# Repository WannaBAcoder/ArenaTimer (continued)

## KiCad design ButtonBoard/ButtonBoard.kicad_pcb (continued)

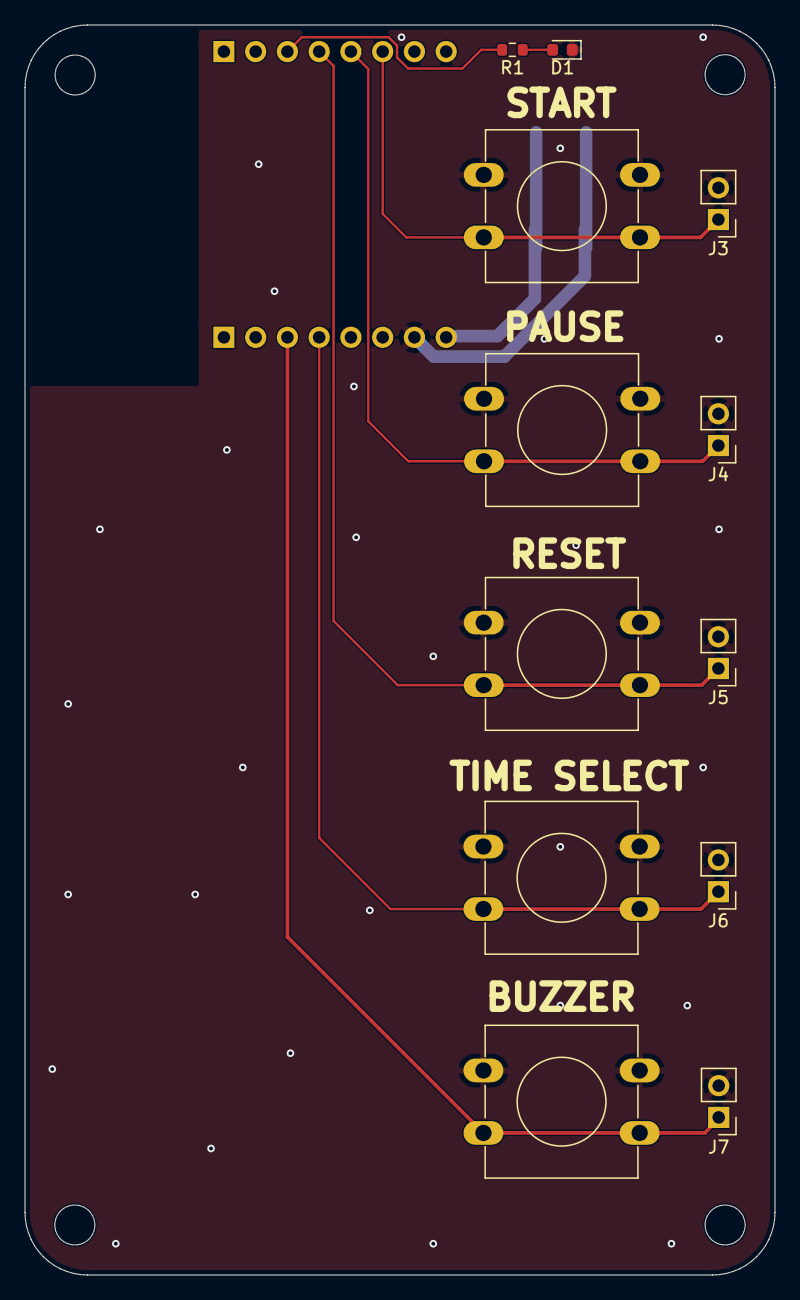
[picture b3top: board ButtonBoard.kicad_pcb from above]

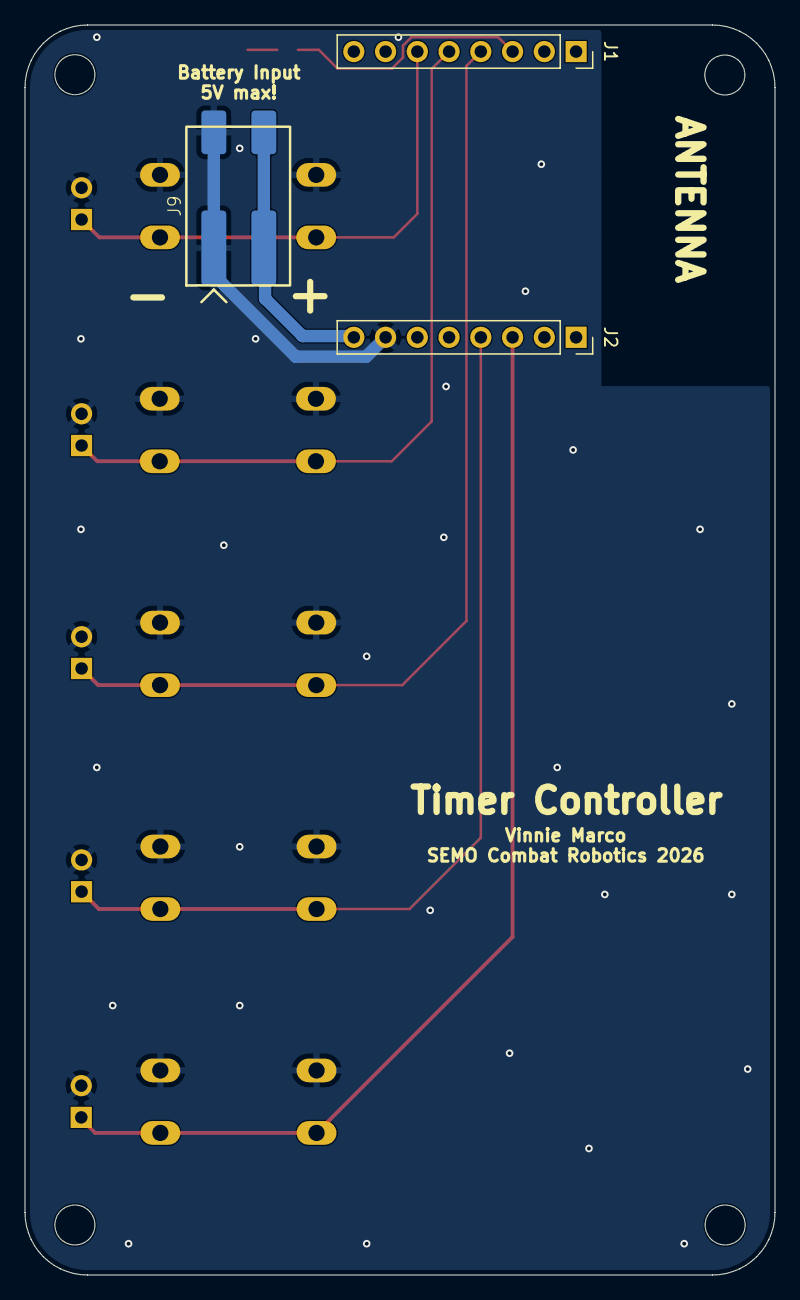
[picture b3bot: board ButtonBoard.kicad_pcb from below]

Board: 2 copper layers, 60.0 x 100.0 mm, 19 parts (3 on the bottom side), 9 nets.

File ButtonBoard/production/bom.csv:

Designator,Footprint,Quantity,Value,LCSC Part #
D1,0603,1,Red,C2286
"J1, J2",PinSocket_1x08_P2.54mm_Vertical,2,Conn_01x08_Socket,C42431840
J9,2060-452_998-404,1,WAGO,C2765055
R1,0603,1,470,C23179
SW1,SW_PUSH-12mm,1,START,C2888699 
SW2,SW_PUSH-12mm,1,PAUSE,C2888699 
SW3,SW_PUSH-12mm,1,RESET,C2888699 
SW4,SW_PUSH-12mm,1,TIME_SEL,C2888699 
SW5,SW_PUSH-12mm,1,BUZZER,C2888699

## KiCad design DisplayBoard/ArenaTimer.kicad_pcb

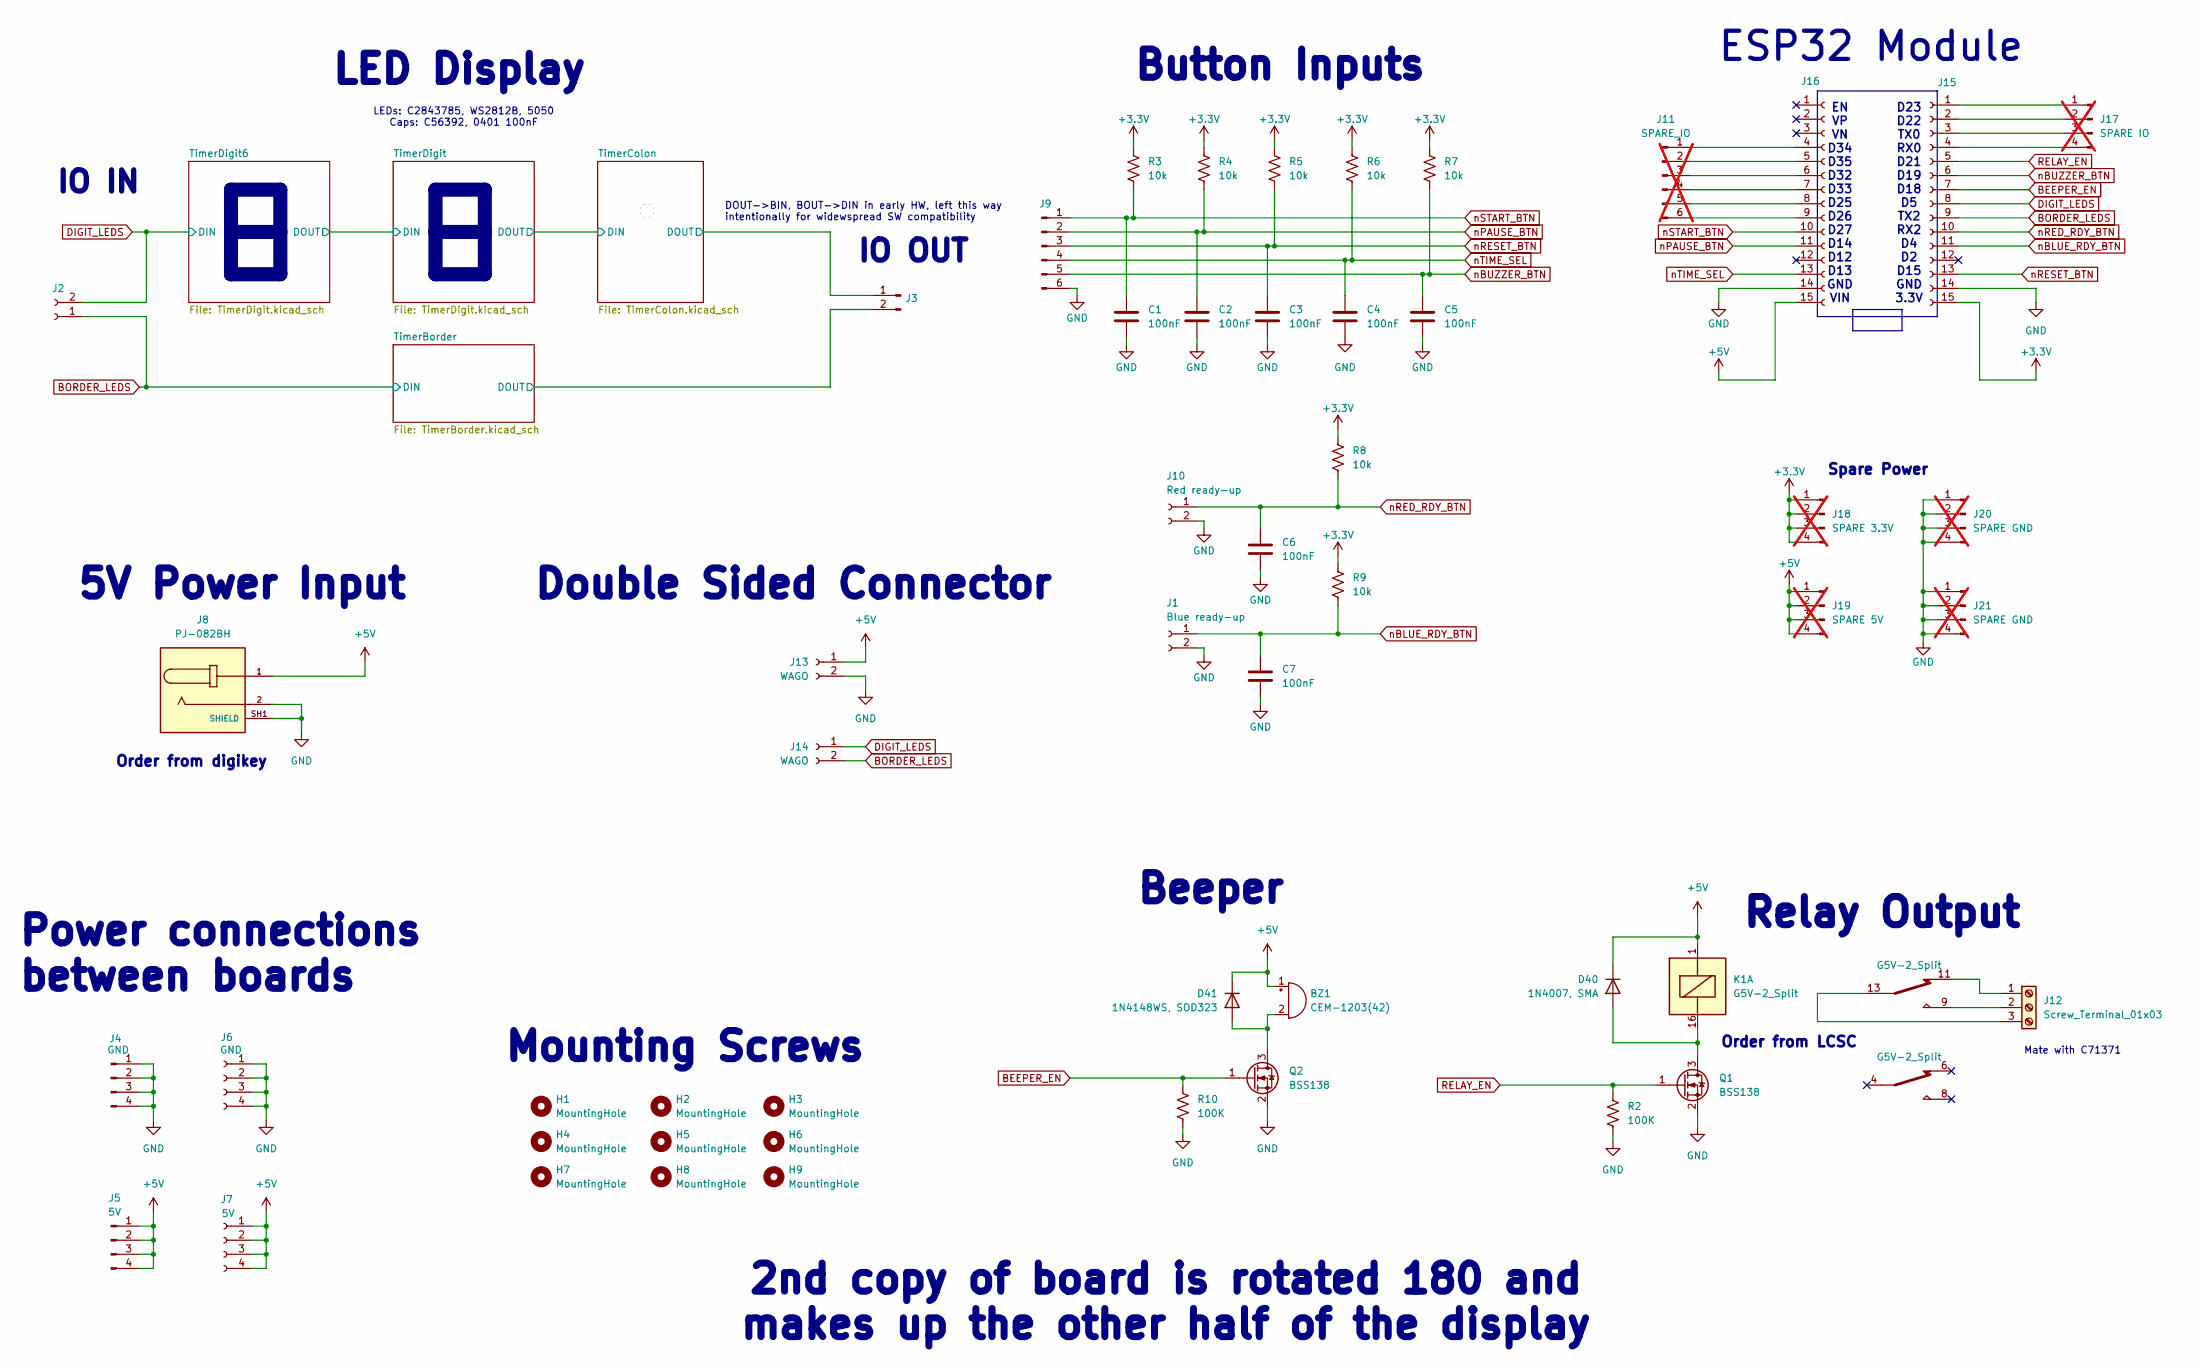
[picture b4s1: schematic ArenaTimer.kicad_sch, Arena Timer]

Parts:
BZ1: CEM-1203(42); Buzzer_TDK_PS1240P02BT_D12.2mm_H6.5mm; LCSC C3812098
C1, C2, C3, C4, C5, C6, C7: 100nF; C_0402_1005Metric; LCSC C1581
D40: 1N4007, SMA; D_SMA; LCSC C727081
D41: 1N4148WS, SOD323; D_SOD-323; LCSC C2128
H1, H2, H3, H4, H5, H6, H7, H8, H9: MountingHole; MountingHole_3.2mm_M3
J1: Blue ready-up; JST_EH_S2B-EH_1x02_P2.50mm_Horizontal; LCSC C19271377
J2: Conn_01x02_Socket; PinSocket_1x02_P2.54mm_Horizontal; LCSC C2897384
J3: Conn_01x02_Pin; PinHeader_1x02_P2.54mm_Horizontal; LCSC C492410
J4: GND; PinHeader_1x04_P2.54mm_Horizontal; LCSC C492412
J5: 5V; PinHeader_1x04_P2.54mm_Horizontal; LCSC C492412
J6: GND; PinSocket_1x04_P2.54mm_Horizontal; LCSC C2897386
J7: 5V; PinSocket_1x04_P2.54mm_Horizontal; LCSC C2897386
J8: PJ-082BH; SAMESKY_PJ-082BH; PARTREV 1.06; LCSC C3094233
J9: Conn_01x06_Pin; JST_EH_S6B-EH_1x06_P2.50mm_Horizontal; LCSC C157919
J10: Red ready-up; JST_EH_S2B-EH_1x02_P2.50mm_Horizontal; LCSC C19271377
J11: SPARE_IO; PinHeader_1x06_P2.54mm_Vertical; not fitted
J12: Screw_Terminal_01x03; TerminalBlock_MaiXu_MX126-5.0-03P_1x03_P5.00mm; LCSC C8377
J13, J14: WAGO; 2060-452_998-404; LCSC C2765055
J15, J16: Conn_01x15_Socket; PinSocket_1x15_P2.54mm_Vertical; LCSC C124408
J17: SPARE IO; PinHeader_1x04_P2.54mm_Vertical; not fitted
J18: SPARE 3.3V; PinHeader_1x04_P2.54mm_Vertical; not fitted
J19: SPARE 5V; PinHeader_1x04_P2.54mm_Vertical; not fitted
J20, J21: SPARE GND; PinHeader_1x04_P2.54mm_Vertical; not fitted
K1: G5V-2_Split; Relay_DPDT_Omron_G5V-2; LCSC C27269
Q1, Q2: BSS138; SOT-323_SC-70; LCSC C5224279
R2, R10: 100K; R_0402_1005Metric; LCSC C25530
R3, R4, R5, R6, R7, R8, R9: 10k; R_0402_1005Metric; LCSC C25744

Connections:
+3.3V: J15.15, J18.1, J18.2, J18.3, J18.4, R3.1, R4.1, R5.1, R6.1, R7.1, R8.1, R9.1
+5V: BZ1.1 (+), D40.1 (K), D41.1 (K), J5.1, J5.2, J5.3, J5.4, J7.1, J7.2, J7.3, J7.4, J8.1, J13.1, J16.15, J19.1, J19.2, J19.3, J19.4, K1.1; also elsewhere on the board
/TimerBorder/DOUT: J3.2; also elsewhere on the board
/TimerColon/DOUT: J3.1; also elsewhere on the board
BEEPER_EN: J15.7, Q2.1 (G), R10.1
BORDER_LEDS: J2.1, J14.2, J15.9; also elsewhere on the board
DIGIT_LEDS: J2.2, J14.1, J15.8; also elsewhere on the board
GND: C1.2, C2.2, C3.2, C4.2, C5.2, C6.2, C7.2, J1.2, J4.1, J4.2, J4.3, J4.4, J6.1, J6.2, J6.3, J6.4, J8.2, J8.SH1 (SHIELD), J8.SH2 (SHIELD), J8.SH3 (SHIELD), J8.SH4 (SHIELD), J9.6, J10.2, J13.2, J15.14, J16.14, J20.1, J20.2, J20.3, J20.4, J21.1, J21.2, J21.3, J21.4, Q1.2 (S), Q2.2 (S), R2.2, R10.2; also elsewhere on the board
unnamed: BZ1.2 (-), D41.2 (A), Q2.3 (D)
unnamed: D40.2 (A), K1.16, Q1.3 (D)
unnamed: J11.1, J16.4
unnamed: J11.2, J16.5
unnamed: J11.3, J16.6
unnamed: J11.4, J16.7
unnamed: J11.5, J16.8
unnamed: J11.6, J16.9
unnamed: J12.1, K1.11
unnamed: J12.2, K1.9
unnamed: J12.3, K1.13
unnamed: J15.1, J17.1
unnamed: J15.2, J17.2
unnamed: J15.3, J17.3
unnamed: J15.4, J17.4
RELAY_EN: J15.5, Q1.1 (G), R2.1
nBLUE_RDY_BTN: C7.1, J1.1, J15.11, R9.2
nBUZZER_BTN: C5.1, J9.5, J15.6, R7.2
nPAUSE_BTN: C2.1, J9.2, J16.11, R4.2
nRED_RDY_BTN: C6.1, J10.1, J15.10, R8.2
nRESET_BTN: C3.1, J9.3, J15.13, R5.2
nSTART_BTN: C1.1, J9.1, J16.10, R3.2
nTIME_SEL: C4.1, J9.4, J16.13, R6.2

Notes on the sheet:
Spare Power
EN VP VN D34 D35 D32 D33 D25 D26 D27 D14 D12 D13 GND VIN
Order from digikey
Mate with C71371
IO IN
Beeper
Power connections between boards
5V Power Input
Order from LCSC
IO OUT
Double Sided Connector
2nd copy of board is rotated 180 and makes up the other half of the display
Relay Output
Button Inputs
Mounting Screws
D23 D22 TX0 RX0 D21 D19 D18 D5 TX2 RX2 D4 D2 D15 GND 3.3V
LEDs: C2843785, WS2812B, 5050 Caps: C56392, 0401 100nF
ESP32 Module
DOUT->BIN, BOUT->DIN in early HW, left this way intentionally for widewspread SW compatibility
LED Display

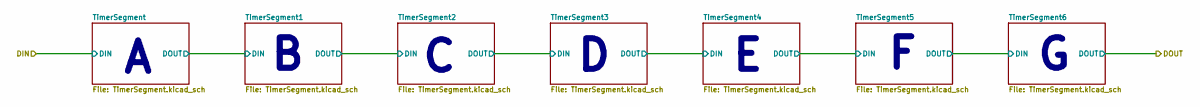
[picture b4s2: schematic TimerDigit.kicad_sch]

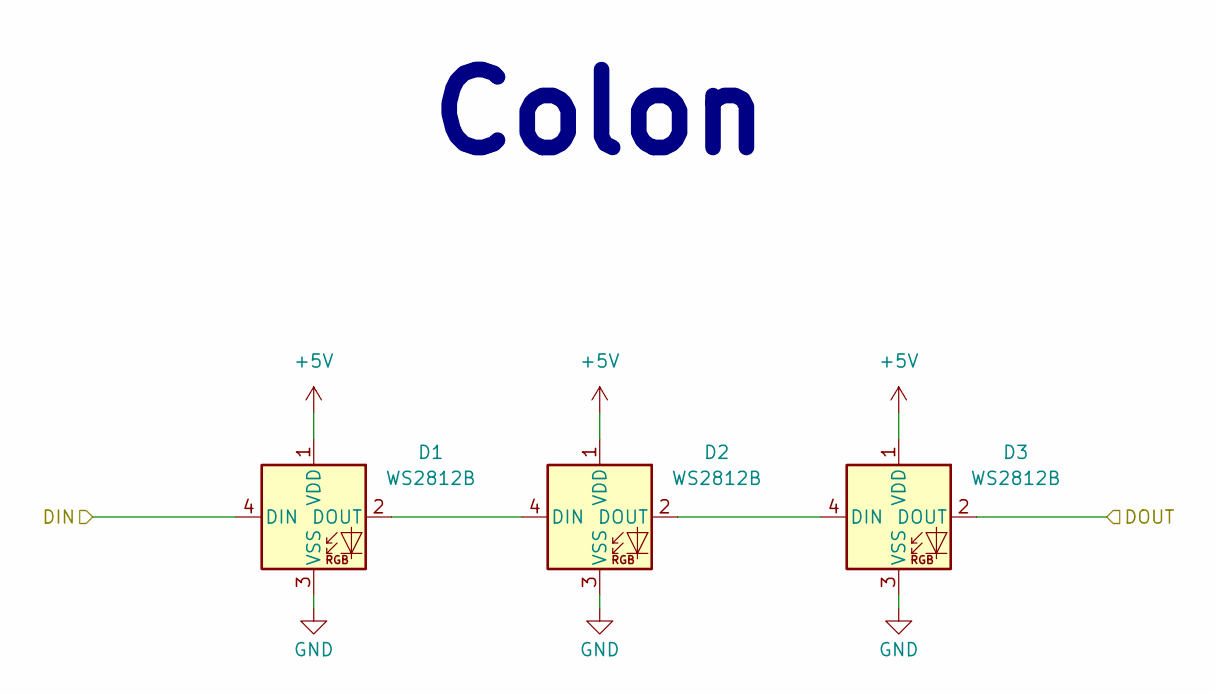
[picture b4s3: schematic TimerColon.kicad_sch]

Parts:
D1, D2, D3: WS2812B; LED_WS2812B_PLCC4_5.0x5.0mm_P3.2mm; LCSC C2843785

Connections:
+5V: D1.1 (VDD), D2.1 (VDD), D3.1 (VDD); also elsewhere on the board
/TimerColon/DIN: D1.4 (DIN); also elsewhere on the board
/TimerColon/DOUT: D3.2 (DOUT); also elsewhere on the board
GND: D1.3 (VSS), D2.3 (VSS), D3.3 (VSS); also elsewhere on the board
unnamed: D1.2 (DOUT), D2.4 (DIN)
unnamed: D2.2 (DOUT), D3.4 (DIN)

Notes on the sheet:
Colon

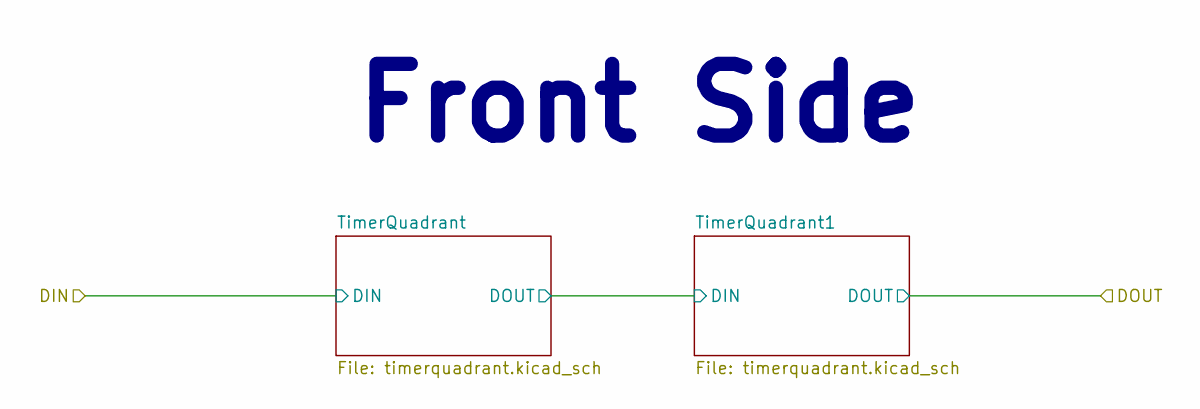
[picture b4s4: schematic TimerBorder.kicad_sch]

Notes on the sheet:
Front Side

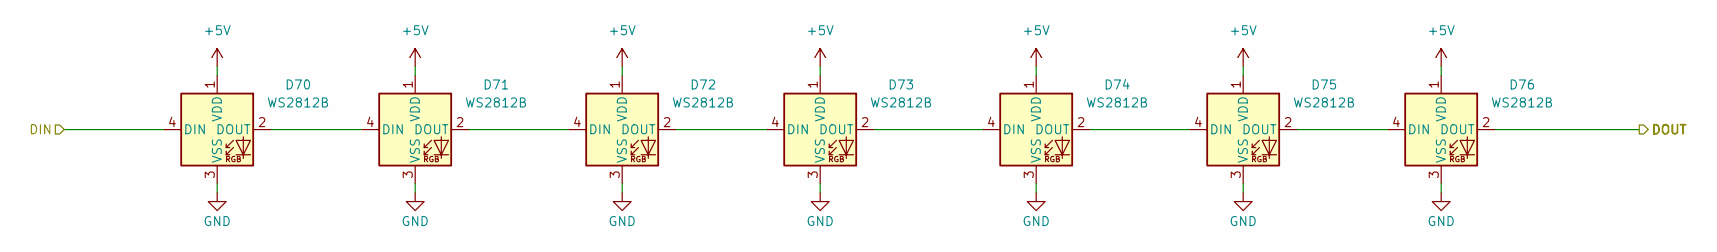
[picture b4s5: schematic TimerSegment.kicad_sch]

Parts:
D70, D71, D72, D73, D74, D75, D76: WS2812B; LED_WS2812B_PLCC4_5.0x5.0mm_P3.2mm; LCSC C2843785

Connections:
+5V: D70.1 (VDD), D71.1 (VDD), D72.1 (VDD), D73.1 (VDD), D74.1 (VDD), D75.1 (VDD), D76.1 (VDD); also elsewhere on the board
/TimerDigit/DIN: D70.4 (DIN); also elsewhere on the board
/TimerDigit/TimerSegment/DOUT: D76.2 (DOUT); also elsewhere on the board
GND: D70.3 (VSS), D71.3 (VSS), D72.3 (VSS), D73.3 (VSS), D74.3 (VSS), D75.3 (VSS), D76.3 (VSS); also elsewhere on the board
unnamed: D70.2 (DOUT), D71.4 (DIN)
unnamed: D71.2 (DOUT), D72.4 (DIN)
unnamed: D72.2 (DOUT), D73.4 (DIN)
unnamed: D73.2 (DOUT), D74.4 (DIN)
unnamed: D74.2 (DOUT), D75.4 (DIN)
unnamed: D75.2 (DOUT), D76.4 (DIN)

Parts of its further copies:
D77, D78, D79, D80, D81, D82, D83, D112, D113, D114, D115, D116, D117, D118, D154, D155, D156, D157, D158, D159, D160, D238, D239, D240, D241, D242, D243, D244, D245, D246, D247, D248, D249, D250, D251, D287, D288, D289, D290, D291, D292, D293, D294, D295, D296, D297, D298, D299, D300, D301, D302, D303, D304, D305, D306, D307, D308, D309, D310, D311, D312, D313, D314, D315, D316, D317, D318, D319, D320, D321, D322, D323, D324, D325, D326, D327, D328, D329, D330, D331, D332, D333, D334, D335, D336, D337, D338, D339, D340, D341, D342: WS2812B; LED_WS2812B_PLCC4_5.0x5.0mm_P3.2mm; LCSC C2843785

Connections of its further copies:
+5V: D77.1 (VDD), D78.1 (VDD), D79.1 (VDD), D80.1 (VDD), D81.1 (VDD), D82.1 (VDD), D83.1 (VDD), D112.1 (VDD), D113.1 (VDD), D114.1 (VDD), D115.1 (VDD), D116.1 (VDD), D117.1 (VDD), D118.1 (VDD), D154.1 (VDD), D155.1 (VDD), D156.1 (VDD), D157.1 (VDD), D158.1 (VDD), D159.1 (VDD), D160.1 (VDD), D238.1 (VDD), D239.1 (VDD), D240.1 (VDD), D241.1 (VDD), D242.1 (VDD), D243.1 (VDD), D244.1 (VDD), D245.1 (VDD), D246.1 (VDD), D247.1 (VDD), D248.1 (VDD), D249.1 (VDD), D250.1 (VDD), D251.1 (VDD), D287.1 (VDD), D288.1 (VDD), D289.1 (VDD), D290.1 (VDD), D291.1 (VDD), D292.1 (VDD), D293.1 (VDD), D294.1 (VDD), D295.1 (VDD), D296.1 (VDD), D297.1 (VDD), D298.1 (VDD), D299.1 (VDD), D300.1 (VDD), D301.1 (VDD), D302.1 (VDD), D303.1 (VDD), D304.1 (VDD), D305.1 (VDD), D306.1 (VDD), D307.1 (VDD), D308.1 (VDD), D309.1 (VDD), D310.1 (VDD), D311.1 (VDD), D312.1 (VDD), D313.1 (VDD), D314.1 (VDD), D315.1 (VDD), D316.1 (VDD), D317.1 (VDD), D318.1 (VDD), D319.1 (VDD), D320.1 (VDD), D321.1 (VDD), D322.1 (VDD), D323.1 (VDD), D324.1 (VDD), D325.1 (VDD), D326.1 (VDD), D327.1 (VDD), D328.1 (VDD), D329.1 (VDD), D330.1 (VDD), D331.1 (VDD), D332.1 (VDD), D333.1 (VDD), D334.1 (VDD), D335.1 (VDD), D336.1 (VDD), D337.1 (VDD), D338.1 (VDD), D339.1 (VDD), D340.1 (VDD), D341.1 (VDD), D342.1 (VDD); also elsewhere on the board
/TimerColon/DIN: D293.2 (DOUT); also elsewhere on the board
/TimerDigit6/TimerSegment1/DOUT: D308.4 (DIN), D342.2 (DOUT)
/TimerDigit6/TimerSegment2/DOUT: D301.4 (DIN), D314.2 (DOUT)
/TimerDigit6/TimerSegment3/DOUT: D294.4 (DIN), D307.2 (DOUT)
/TimerDigit6/TimerSegment4/DOUT: D300.2 (DOUT), D322.4 (DIN)
/TimerDigit6/TimerSegment5/DOUT: D315.4 (DIN), D328.2 (DOUT)
/TimerDigit6/TimerSegment/DOUT: D335.2 (DOUT), D336.4 (DIN)
/TimerDigit/DIN: D321.2 (DOUT); also elsewhere on the board
/TimerDigit/TimerSegment1/DOUT: D83.2 (DOUT), D112.4 (DIN)
/TimerDigit/TimerSegment2/DOUT: D118.2 (DOUT), D154.4 (DIN)
/TimerDigit/TimerSegment3/DOUT: D160.2 (DOUT), D238.4 (DIN)
/TimerDigit/TimerSegment4/DOUT: D244.2 (DOUT), D245.4 (DIN)
/TimerDigit/TimerSegment5/DOUT: D251.2 (DOUT), D287.4 (DIN)
/TimerDigit/TimerSegment/DOUT: D77.4 (DIN); also elsewhere on the board
DIGIT_LEDS: D329.4 (DIN); also elsewhere on the board
GND: D77.3 (VSS), D78.3 (VSS), D79.3 (VSS), D80.3 (VSS), D81.3 (VSS), D82.3 (VSS), D83.3 (VSS), D112.3 (VSS), D113.3 (VSS), D114.3 (VSS), D115.3 (VSS), D116.3 (VSS), D117.3 (VSS), D118.3 (VSS), D154.3 (VSS), D155.3 (VSS), D156.3 (VSS), D157.3 (VSS), D158.3 (VSS), D159.3 (VSS), D160.3 (VSS), D238.3 (VSS), D239.3 (VSS), D240.3 (VSS), D241.3 (VSS), D242.3 (VSS), D243.3 (VSS), D244.3 (VSS), D245.3 (VSS), D246.3 (VSS), D247.3 (VSS), D248.3 (VSS), D249.3 (VSS), D250.3 (VSS), D251.3 (VSS), D287.3 (VSS), D288.3 (VSS), D289.3 (VSS), D290.3 (VSS), D291.3 (VSS), D292.3 (VSS), D293.3 (VSS), D294.3 (VSS), D295.3 (VSS), D296.3 (VSS), D297.3 (VSS), D298.3 (VSS), D299.3 (VSS), D300.3 (VSS), D301.3 (VSS), D302.3 (VSS), D303.3 (VSS), D304.3 (VSS), D305.3 (VSS), D306.3 (VSS), D307.3 (VSS), D308.3 (VSS), D309.3 (VSS), D310.3 (VSS), D311.3 (VSS), D312.3 (VSS), D313.3 (VSS), D314.3 (VSS), D315.3 (VSS), D316.3 (VSS), D317.3 (VSS), D318.3 (VSS), D319.3 (VSS), D320.3 (VSS), D321.3 (VSS), D322.3 (VSS), D323.3 (VSS), D324.3 (VSS), D325.3 (VSS), D326.3 (VSS), D327.3 (VSS), D328.3 (VSS), D329.3 (VSS), D330.3 (VSS), D331.3 (VSS), D332.3 (VSS), D333.3 (VSS), D334.3 (VSS), D335.3 (VSS), D336.3 (VSS), D337.3 (VSS), D338.3 (VSS), D339.3 (VSS), D340.3 (VSS), D341.3 (VSS), D342.3 (VSS); also elsewhere on the board
unnamed: D77.2 (DOUT), D78.4 (DIN)
unnamed: D78.2 (DOUT), D79.4 (DIN)
unnamed: D79.2 (DOUT), D80.4 (DIN)
unnamed: D80.2 (DOUT), D81.4 (DIN)
unnamed: D81.2 (DOUT), D82.4 (DIN)
unnamed: D82.2 (DOUT), D83.4 (DIN)
unnamed: D112.2 (DOUT), D113.4 (DIN)
unnamed: D113.2 (DOUT), D114.4 (DIN)
unnamed: D114.2 (DOUT), D115.4 (DIN)
unnamed: D115.2 (DOUT), D116.4 (DIN)
unnamed: D116.2 (DOUT), D117.4 (DIN)
unnamed: D117.2 (DOUT), D118.4 (DIN)
unnamed: D154.2 (DOUT), D155.4 (DIN)
unnamed: D155.2 (DOUT), D156.4 (DIN)
unnamed: D156.2 (DOUT), D157.4 (DIN)
unnamed: D157.2 (DOUT), D158.4 (DIN)
unnamed: D158.2 (DOUT), D159.4 (DIN)
unnamed: D159.2 (DOUT), D160.4 (DIN)
unnamed: D238.2 (DOUT), D239.4 (DIN)
unnamed: D239.2 (DOUT), D240.4 (DIN)
unnamed: D240.2 (DOUT), D241.4 (DIN)
unnamed: D241.2 (DOUT), D242.4 (DIN)
unnamed: D242.2 (DOUT), D243.4 (DIN)
unnamed: D243.2 (DOUT), D244.4 (DIN)
unnamed: D245.2 (DOUT), D246.4 (DIN)
unnamed: D246.2 (DOUT), D247.4 (DIN)
unnamed: D247.2 (DOUT), D248.4 (DIN)
unnamed: D248.2 (DOUT), D249.4 (DIN)
unnamed: D249.2 (DOUT), D250.4 (DIN)
unnamed: D250.2 (DOUT), D251.4 (DIN)
unnamed: D287.2 (DOUT), D288.4 (DIN)
unnamed: D288.2 (DOUT), D289.4 (DIN)
unnamed: D289.2 (DOUT), D290.4 (DIN)
unnamed: D290.2 (DOUT), D291.4 (DIN)
unnamed: D291.2 (DOUT), D292.4 (DIN)
unnamed: D292.2 (DOUT), D293.4 (DIN)
unnamed: D294.2 (DOUT), D295.4 (DIN)
unnamed: D295.2 (DOUT), D296.4 (DIN)
unnamed: D296.2 (DOUT), D297.4 (DIN)
unnamed: D297.2 (DOUT), D298.4 (DIN)
unnamed: D298.2 (DOUT), D299.4 (DIN)
unnamed: D299.2 (DOUT), D300.4 (DIN)
unnamed: D301.2 (DOUT), D302.4 (DIN)
unnamed: D302.2 (DOUT), D303.4 (DIN)
unnamed: D303.2 (DOUT), D304.4 (DIN)
unnamed: D304.2 (DOUT), D305.4 (DIN)
unnamed: D305.2 (DOUT), D306.4 (DIN)
unnamed: D306.2 (DOUT), D307.4 (DIN)
unnamed: D308.2 (DOUT), D309.4 (DIN)
unnamed: D309.2 (DOUT), D310.4 (DIN)
unnamed: D310.2 (DOUT), D311.4 (DIN)
unnamed: D311.2 (DOUT), D312.4 (DIN)
unnamed: D312.2 (DOUT), D313.4 (DIN)
unnamed: D313.2 (DOUT), D314.4 (DIN)
unnamed: D315.2 (DOUT), D316.4 (DIN)
unnamed: D316.2 (DOUT), D317.4 (DIN)
unnamed: D317.2 (DOUT), D318.4 (DIN)
unnamed: D318.2 (DOUT), D319.4 (DIN)
unnamed: D319.2 (DOUT), D320.4 (DIN)
unnamed: D320.2 (DOUT), D321.4 (DIN)
unnamed: D322.2 (DOUT), D323.4 (DIN)
unnamed: D323.2 (DOUT), D324.4 (DIN)
unnamed: D324.2 (DOUT), D325.4 (DIN)
unnamed: D325.2 (DOUT), D326.4 (DIN)
unnamed: D326.2 (DOUT), D327.4 (DIN)
unnamed: D327.2 (DOUT), D328.4 (DIN)
unnamed: D329.2 (DOUT), D330.4 (DIN)
unnamed: D330.2 (DOUT), D331.4 (DIN)
unnamed: D331.2 (DOUT), D332.4 (DIN)
unnamed: D332.2 (DOUT), D333.4 (DIN)
unnamed: D333.2 (DOUT), D334.4 (DIN)
unnamed: D334.2 (DOUT), D335.4 (DIN)
unnamed: D336.2 (DOUT), D337.4 (DIN)
unnamed: D337.2 (DOUT), D338.4 (DIN)
unnamed: D338.2 (DOUT), D339.4 (DIN)
unnamed: D339.2 (DOUT), D340.4 (DIN)
unnamed: D340.2 (DOUT), D341.4 (DIN)
unnamed: D341.2 (DOUT), D342.4 (DIN)

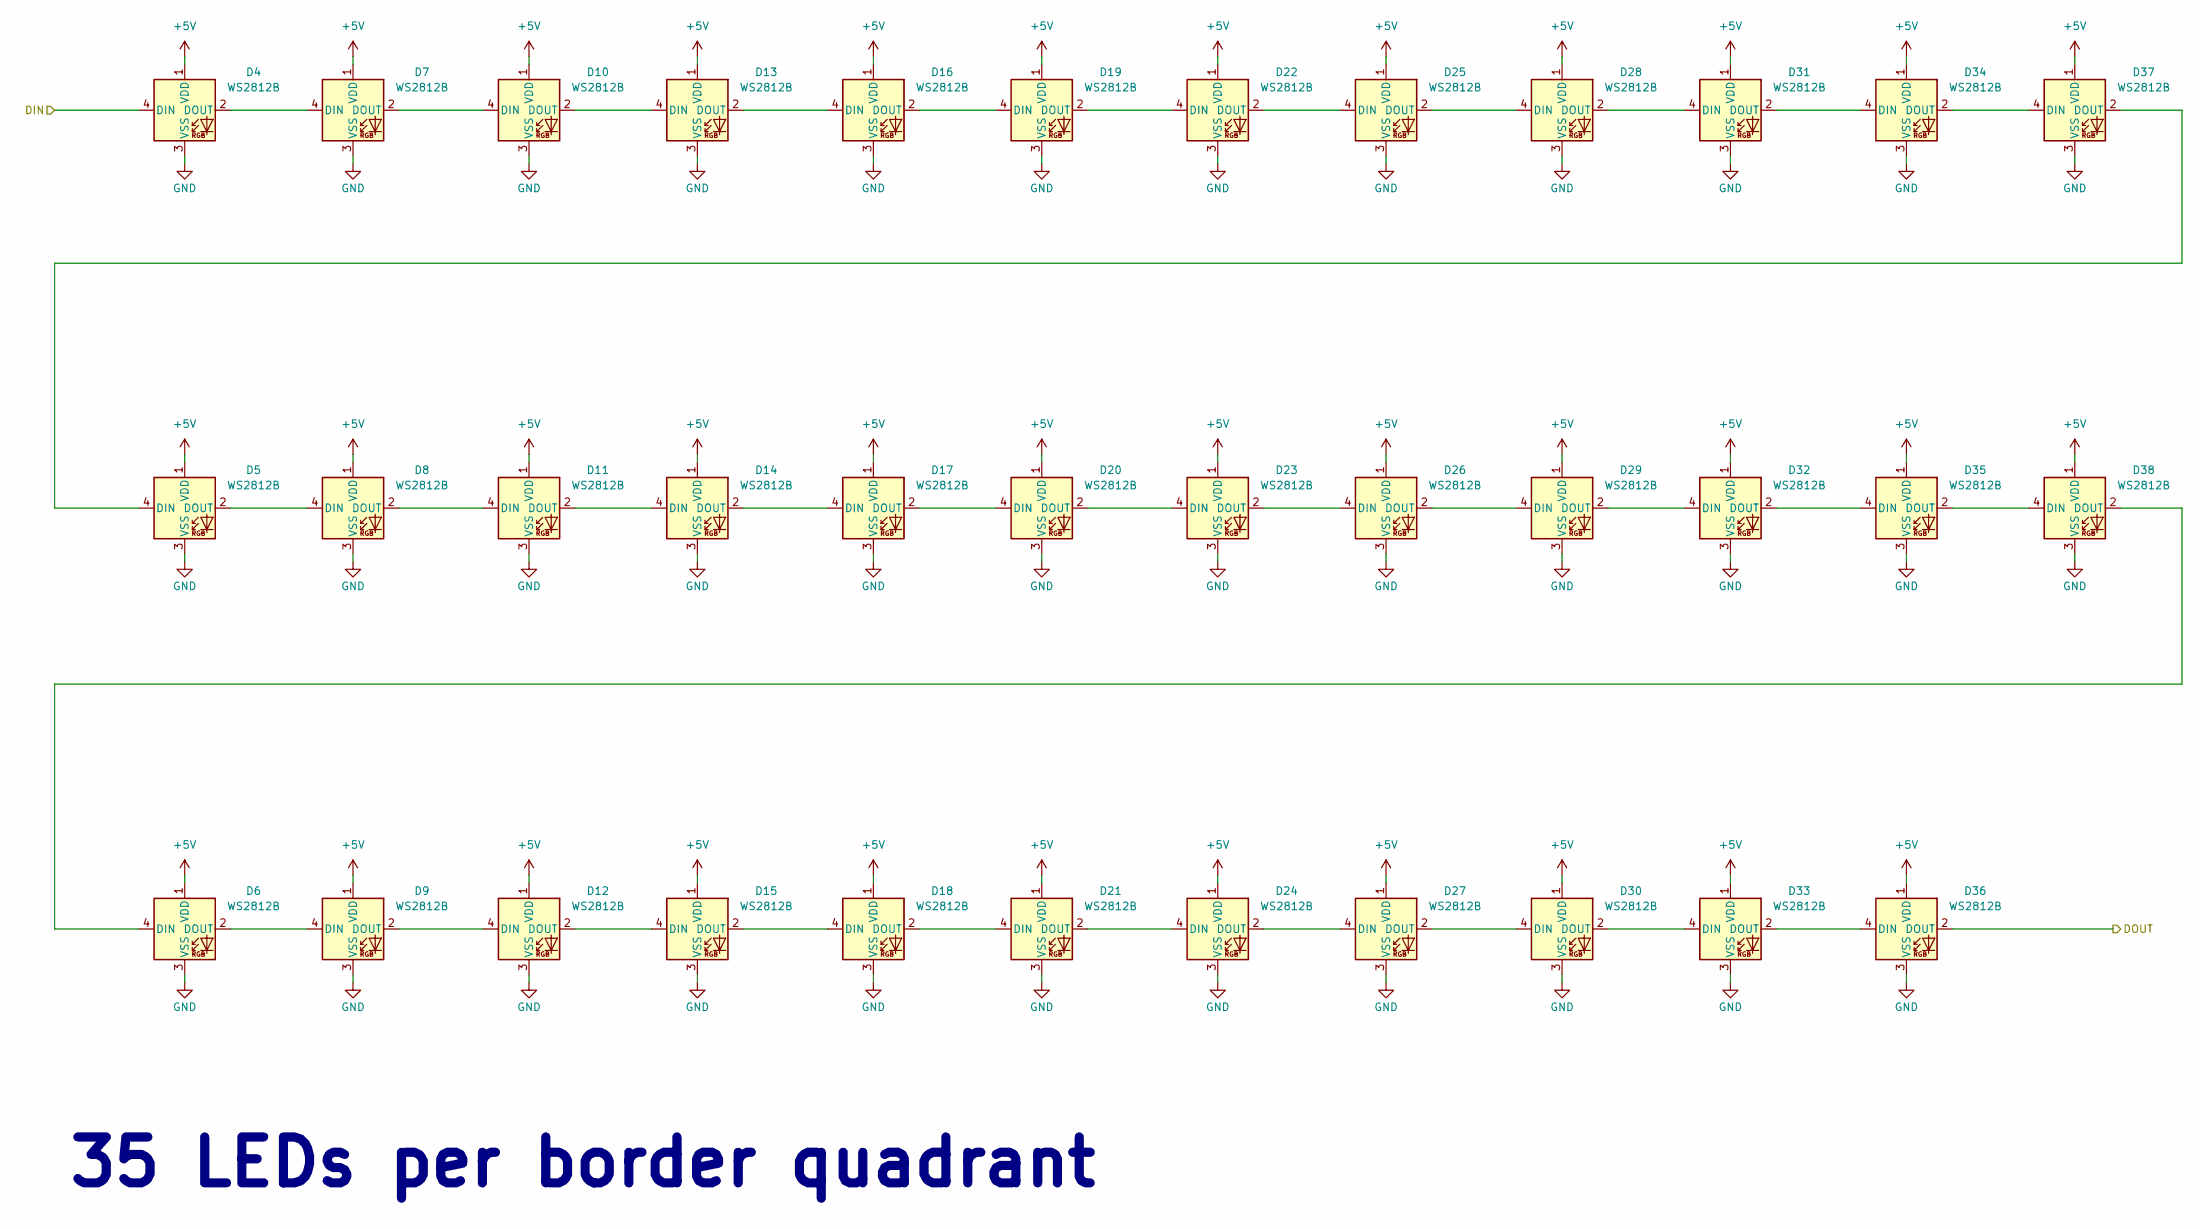
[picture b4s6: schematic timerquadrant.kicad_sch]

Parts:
D4, D5, D6, D7, D8, D9, D10, D11, D12, D13, D14, D15, D16, D17, D18, D19, D20, D21, D22, D23, D24, D25, D26, D27, D28, D29, D30, D31, D32, D33, D34, D35, D36, D37, D38: WS2812B; LED_WS2812B_PLCC4_5.0x5.0mm_P3.2mm; LCSC C2843785

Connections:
+5V: D4.1 (VDD), D5.1 (VDD), D6.1 (VDD), D7.1 (VDD), D8.1 (VDD), D9.1 (VDD), D10.1 (VDD), D11.1 (VDD), D12.1 (VDD), D13.1 (VDD), D14.1 (VDD), D15.1 (VDD), D16.1 (VDD), D17.1 (VDD), D18.1 (VDD), D19.1 (VDD), D20.1 (VDD), D21.1 (VDD), D22.1 (VDD), D23.1 (VDD), D24.1 (VDD), D25.1 (VDD), D26.1 (VDD), D27.1 (VDD), D28.1 (VDD), D29.1 (VDD), D30.1 (VDD), D31.1 (VDD), D32.1 (VDD), D33.1 (VDD), D34.1 (VDD), D35.1 (VDD), D36.1 (VDD), D37.1 (VDD), D38.1 (VDD); also elsewhere on the board
/TimerBorder/DOUT: D36.2 (DOUT); also elsewhere on the board
/TimerBorder/TimerQuadrant/DOUT: D4.4 (DIN); also elsewhere on the board
GND: D4.3 (VSS), D5.3 (VSS), D6.3 (VSS), D7.3 (VSS), D8.3 (VSS), D9.3 (VSS), D10.3 (VSS), D11.3 (VSS), D12.3 (VSS), D13.3 (VSS), D14.3 (VSS), D15.3 (VSS), D16.3 (VSS), D17.3 (VSS), D18.3 (VSS), D19.3 (VSS), D20.3 (VSS), D21.3 (VSS), D22.3 (VSS), D23.3 (VSS), D24.3 (VSS), D25.3 (VSS), D26.3 (VSS), D27.3 (VSS), D28.3 (VSS), D29.3 (VSS), D30.3 (VSS), D31.3 (VSS), D32.3 (VSS), D33.3 (VSS), D34.3 (VSS), D35.3 (VSS), D36.3 (VSS), D37.3 (VSS), D38.3 (VSS); also elsewhere on the board
unnamed: D4.2 (DOUT), D7.4 (DIN)
unnamed: D5.2 (DOUT), D8.4 (DIN)
unnamed: D6.2 (DOUT), D9.4 (DIN)
unnamed: D7.2 (DOUT), D10.4 (DIN)
unnamed: D10.2 (DOUT), D13.4 (DIN)
unnamed: D8.2 (DOUT), D11.4 (DIN)
unnamed: D11.2 (DOUT), D14.4 (DIN)
unnamed: D9.2 (DOUT), D12.4 (DIN)
unnamed: D12.2 (DOUT), D15.4 (DIN)
unnamed: D13.2 (DOUT), D16.4 (DIN)
unnamed: D14.2 (DOUT), D17.4 (DIN)
unnamed: D15.2 (DOUT), D18.4 (DIN)
unnamed: D16.2 (DOUT), D19.4 (DIN)
unnamed: D17.2 (DOUT), D20.4 (DIN)
unnamed: D18.2 (DOUT), D21.4 (DIN)
unnamed: D19.2 (DOUT), D22.4 (DIN)
unnamed: D20.2 (DOUT), D23.4 (DIN)
unnamed: D21.2 (DOUT), D24.4 (DIN)
unnamed: D22.2 (DOUT), D25.4 (DIN)
unnamed: D23.2 (DOUT), D26.4 (DIN)
unnamed: D24.2 (DOUT), D27.4 (DIN)
unnamed: D25.2 (DOUT), D28.4 (DIN)
unnamed: D26.2 (DOUT), D29.4 (DIN)
unnamed: D27.2 (DOUT), D30.4 (DIN)
unnamed: D28.2 (DOUT), D31.4 (DIN)
unnamed: D29.2 (DOUT), D32.4 (DIN)
unnamed: D30.2 (DOUT), D33.4 (DIN)
unnamed: D31.2 (DOUT), D34.4 (DIN)
unnamed: D32.2 (DOUT), D35.4 (DIN)
unnamed: D33.2 (DOUT), D36.4 (DIN)
unnamed: D34.2 (DOUT), D37.4 (DIN)
unnamed: D35.2 (DOUT), D38.4 (DIN)
unnamed: D5.4 (DIN), D37.2 (DOUT)
unnamed: D6.4 (DIN), D38.2 (DOUT)

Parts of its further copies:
D252, D253, D254, D255, D256, D257, D258, D259, D260, D261, D262, D263, D264, D265, D266, D267, D268, D269, D270, D271, D272, D273, D274, D275, D276, D277, D278, D279, D280, D281, D282, D283, D284, D285, D286: WS2812B; LED_WS2812B_PLCC4_5.0x5.0mm_P3.2mm; LCSC C2843785

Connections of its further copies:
+5V: D252.1 (VDD), D253.1 (VDD), D254.1 (VDD), D255.1 (VDD), D256.1 (VDD), D257.1 (VDD), D258.1 (VDD), D259.1 (VDD), D260.1 (VDD), D261.1 (VDD), D262.1 (VDD), D263.1 (VDD), D264.1 (VDD), D265.1 (VDD), D266.1 (VDD), D267.1 (VDD), D268.1 (VDD), D269.1 (VDD), D270.1 (VDD), D271.1 (VDD), D272.1 (VDD), D273.1 (VDD), D274.1 (VDD), D275.1 (VDD), D276.1 (VDD), D277.1 (VDD), D278.1 (VDD), D279.1 (VDD), D280.1 (VDD), D281.1 (VDD), D282.1 (VDD), D283.1 (VDD), D284.1 (VDD), D285.1 (VDD), D286.1 (VDD); also elsewhere on the board
/TimerBorder/TimerQuadrant/DOUT: D284.2 (DOUT); also elsewhere on the board
BORDER_LEDS: D252.4 (DIN); also elsewhere on the board
GND: D252.3 (VSS), D253.3 (VSS), D254.3 (VSS), D255.3 (VSS), D256.3 (VSS), D257.3 (VSS), D258.3 (VSS), D259.3 (VSS), D260.3 (VSS), D261.3 (VSS), D262.3 (VSS), D263.3 (VSS), D264.3 (VSS), D265.3 (VSS), D266.3 (VSS), D267.3 (VSS), D268.3 (VSS), D269.3 (VSS), D270.3 (VSS), D271.3 (VSS), D272.3 (VSS), D273.3 (VSS), D274.3 (VSS), D275.3 (VSS), D276.3 (VSS), D277.3 (VSS), D278.3 (VSS), D279.3 (VSS), D280.3 (VSS), D281.3 (VSS), D282.3 (VSS), D283.3 (VSS), D284.3 (VSS), D285.3 (VSS), D286.3 (VSS); also elsewhere on the board
unnamed: D252.2 (DOUT), D255.4 (DIN)
unnamed: D253.4 (DIN), D285.2 (DOUT)
unnamed: D253.2 (DOUT), D256.4 (DIN)
unnamed: D254.4 (DIN), D286.2 (DOUT)
unnamed: D254.2 (DOUT), D257.4 (DIN)
unnamed: D255.2 (DOUT), D258.4 (DIN)
unnamed: D256.2 (DOUT), D259.4 (DIN)
unnamed: D257.2 (DOUT), D260.4 (DIN)
unnamed: D258.2 (DOUT), D261.4 (DIN)
unnamed: D259.2 (DOUT), D262.4 (DIN)
unnamed: D260.2 (DOUT), D263.4 (DIN)
unnamed: D261.2 (DOUT), D264.4 (DIN)
unnamed: D262.2 (DOUT), D265.4 (DIN)
unnamed: D263.2 (DOUT), D266.4 (DIN)
unnamed: D264.2 (DOUT), D267.4 (DIN)
unnamed: D265.2 (DOUT), D268.4 (DIN)
unnamed: D266.2 (DOUT), D269.4 (DIN)
unnamed: D267.2 (DOUT), D270.4 (DIN)
unnamed: D268.2 (DOUT), D271.4 (DIN)
unnamed: D269.2 (DOUT), D272.4 (DIN)
unnamed: D270.2 (DOUT), D273.4 (DIN)
unnamed: D271.2 (DOUT), D274.4 (DIN)
unnamed: D272.2 (DOUT), D275.4 (DIN)
unnamed: D273.2 (DOUT), D276.4 (DIN)
unnamed: D274.2 (DOUT), D277.4 (DIN)
unnamed: D275.2 (DOUT), D278.4 (DIN)
unnamed: D276.2 (DOUT), D279.4 (DIN)
unnamed: D277.2 (DOUT), D280.4 (DIN)
unnamed: D278.2 (DOUT), D281.4 (DIN)
unnamed: D279.2 (DOUT), D282.4 (DIN)
unnamed: D280.2 (DOUT), D283.4 (DIN)
unnamed: D281.2 (DOUT), D284.4 (DIN)
unnamed: D282.2 (DOUT), D285.4 (DIN)
unnamed: D283.2 (DOUT), D286.4 (DIN)

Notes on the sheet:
35 LEDs per border quadrant
